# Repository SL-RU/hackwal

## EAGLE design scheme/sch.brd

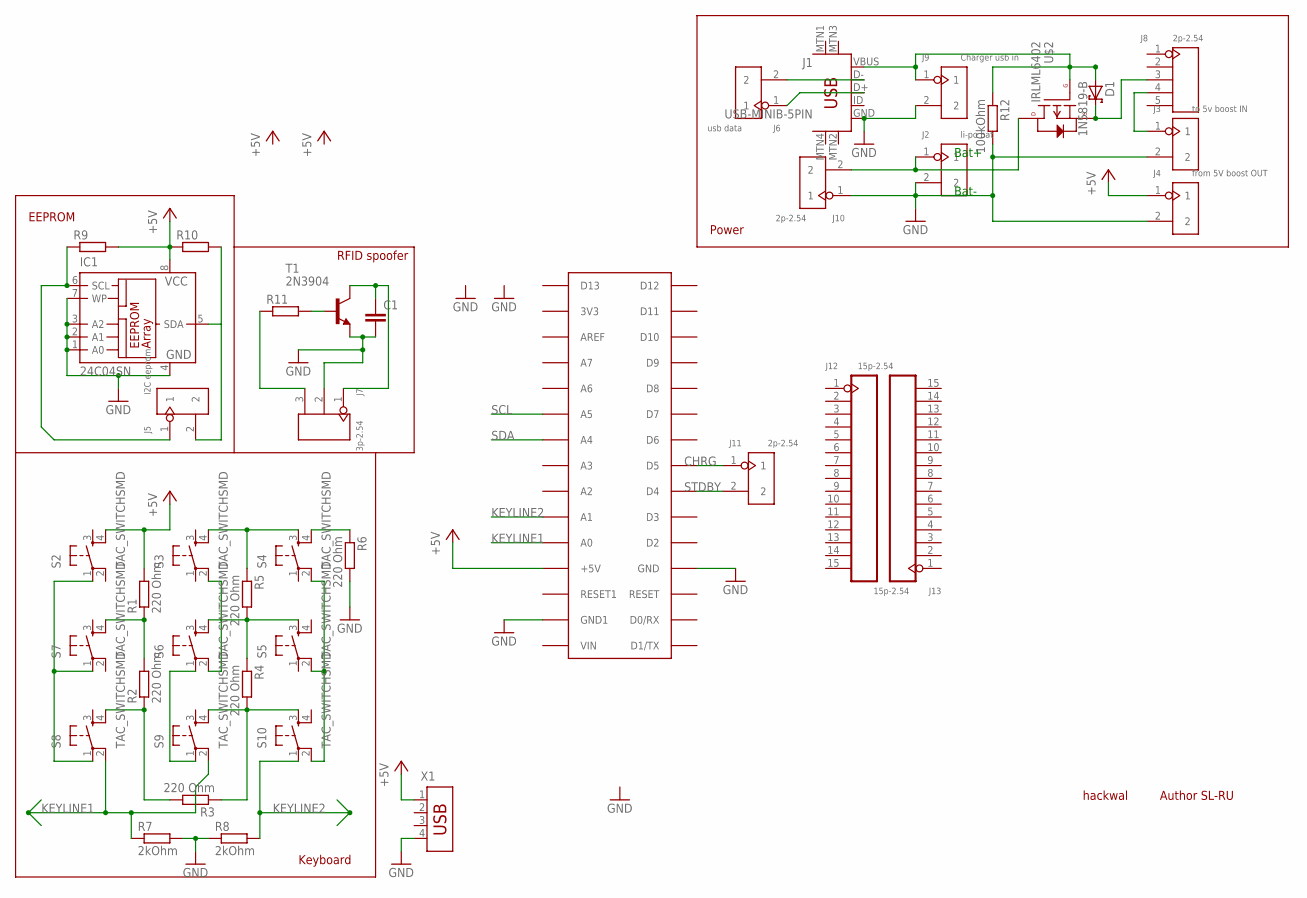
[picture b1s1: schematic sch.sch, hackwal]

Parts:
C1: C5/3; C5B3
D1: 1N5819-B; DO41-7.6
IC1: 24C04SN; SO-08
J1: USB-MINIB-5PIN; USB-MINIB
J2: li-po bat; H2-2.54
J3: to 5v boost IN; H2-2.54
J4: from 5V boost OUT; H2-2.54
J5: I2C eeprom; H2-2.54
J6: usb data; H2-2.54
J7: 3p-2.54; H3-2.54
J8: 2p-2.54; H5-2.54
J9: Charger usb in; H2-2.54
J10, J11: 2p-2.54; H2-2.54
J12, J13: 15p-2.54; H15-2.54
R1, R2, R3, R4, R5, R6: 220 Ohm; 0207/10
R7, R8: 2kOhm; 0207/10
R9, R10, R11: R-EU_0207/10; 0207/10
R12: 100kOhm; 0207/10
S2, S3, S4, S5, S6, S7, S8, S9, S10: TAC_SWITCHSMD; TACTILE-SWITCH-SMD
T1: 2N3904; TO92
U$1: ARDUINONANO; PDIP-32
U$2: IRLML6402; SOT23-3
X1: USB-787616; USB

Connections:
+5V: IC1.8 (VCC), J4.1, R1.2, R9.2, R10.1, S2.4, U$1.+5V, X1.1
CHRG: J11.1, U$1.D5
DDDASD: IC1.5 (SDA), J5.2, R10.2
DDSADSADF: IC1.6 (SCL), J5.1, R9.1
GND: C1.2, IC1.1 (A0), IC1.2 (A1), IC1.3 (A2), IC1.4 (GND), IC1.7 (WP), J1.GND, J2.2, J3.2, J4.2, J7.2, J9.2, J10.1, R6.2, R7.2, R8.1, R12.2, T1.3 (E), U$1.GND, U$1.GND1, X1.4
KEYLINE1: R7.1, S8.2, S9.2, U$1.A0
KEYLINE2: R8.2, S10.1, U$1.A1
unnamed: R6.1, S4.4
unnamed: R5.1, S3.4, S4.3
unnamed: S4.2, S5.2, S10.2
unnamed: R4.1, R5.2, S5.3, S6.4
unnamed: S3.2, S6.2
unnamed: S6.1, S9.1
unnamed: R3.1, R4.2, S9.4, S10.3
unnamed: R2.1, R3.2, S8.4
unnamed: R1.1, R2.2, S7.4
unnamed: D1.A, J1.VBUS, J9.1, R12.1, U$2.1 (G)
unnamed: S2.1, S7.1, S8.1
unnamed: J2.1, J10.2, U$2.3 (D)
unnamed: J1.D-, J6.2
unnamed: D1.C, J8.3, U$2.2 (S)
unnamed: J1.D+, J6.1
unnamed: J3.1, J8.4
unnamed: R11.2, T1.2 (B)
unnamed: C1.1, J7.1, T1.1 (C)
unnamed: J7.3, R11.1
SCL: U$1.A5
SDA: U$1.A4
STDBY: J11.2, U$1.D4

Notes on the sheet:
Bat+
Bat-
Power
RFID spoofer
EEPROM
Keyboard
hackwal
Author SL-RU

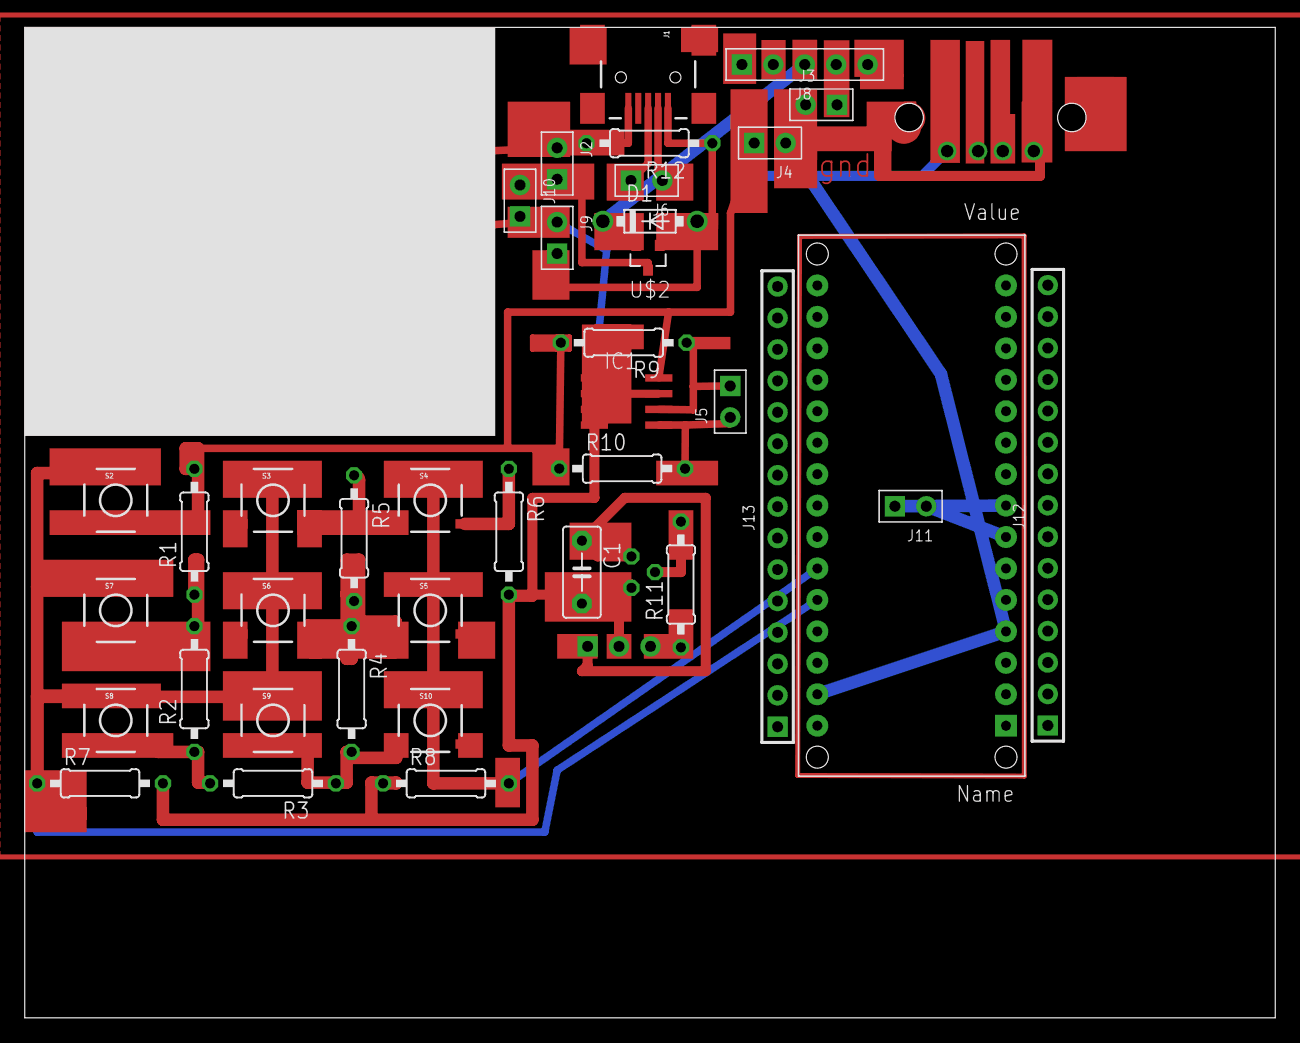
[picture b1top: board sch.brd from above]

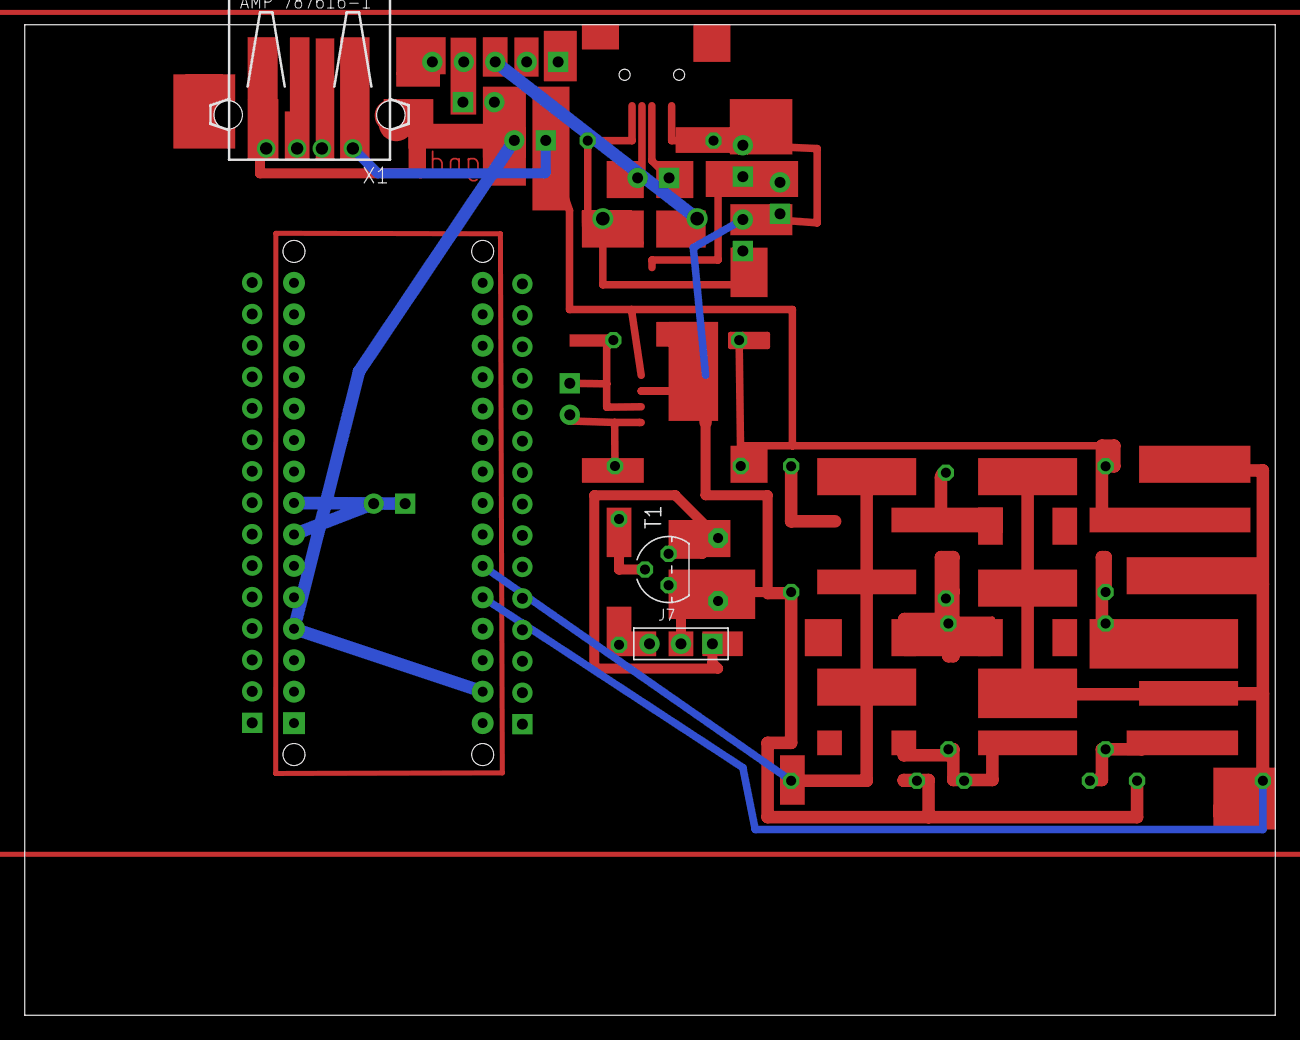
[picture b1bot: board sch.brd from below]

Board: 2 copper layers, 101.0 x 80.0 mm, 41 parts (3 on the bottom side), 27 nets.

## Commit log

2015-11-16 App switching
2015-11-28 Added scheme
2015-11-30 battery status
2015-12-01 Some fixes and documentation
2015-12-04 Optimization, ibutton app, note app
2015-12-06 FUUUUUUUUUUUUUUUUUUU!!!!1111111111111 FUUUUUUUUUUUUUUUUUUUUUUUUUUUUUUUUUUUUUUUUUU There are some unexplainable errors!11 I think it is because of ROM ends, but I couldn't solve it.
    I give up. =c

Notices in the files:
parts and their libraries:
SparkFun-Connectors: Licensing: Creative Commons ShareAlike 4.0 International - https://creativecommons.org/licenses/by-sa/4.0
